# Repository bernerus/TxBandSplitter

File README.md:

# TxBandSplitter
SDR Transmit band splitter and amplifier for VHF/UHF bands. A KiCad + Python project.

The aim of this project is to create an intermediate transmit driver stage that 
takes the RF level of an SDR transmitter from around 1 dBm to around +30 dBm.
Doing this would probably be illegal except for licensed radio amateurs, but
such equipment should nevertheless work only on the amateur bands.
This device takes 1 dBm RF from e.g. a HackRF transceiver, splits the output on
either the 50, 144, 432 och 1295 MHz bands and takes the output level to about +30 dBm or 1 W.
The amplification is done in two steps with the filtering and a programmable attenuator in between,
The final RF is the again split on 4 outputs usein PIN diodes.

The band selection, amplifier power and level of attenuation is controlled over an I2C connection
suitable for connectiong to a RaspBerry PI computer.

Sample software for controlling the device from an RPI is written in Python.

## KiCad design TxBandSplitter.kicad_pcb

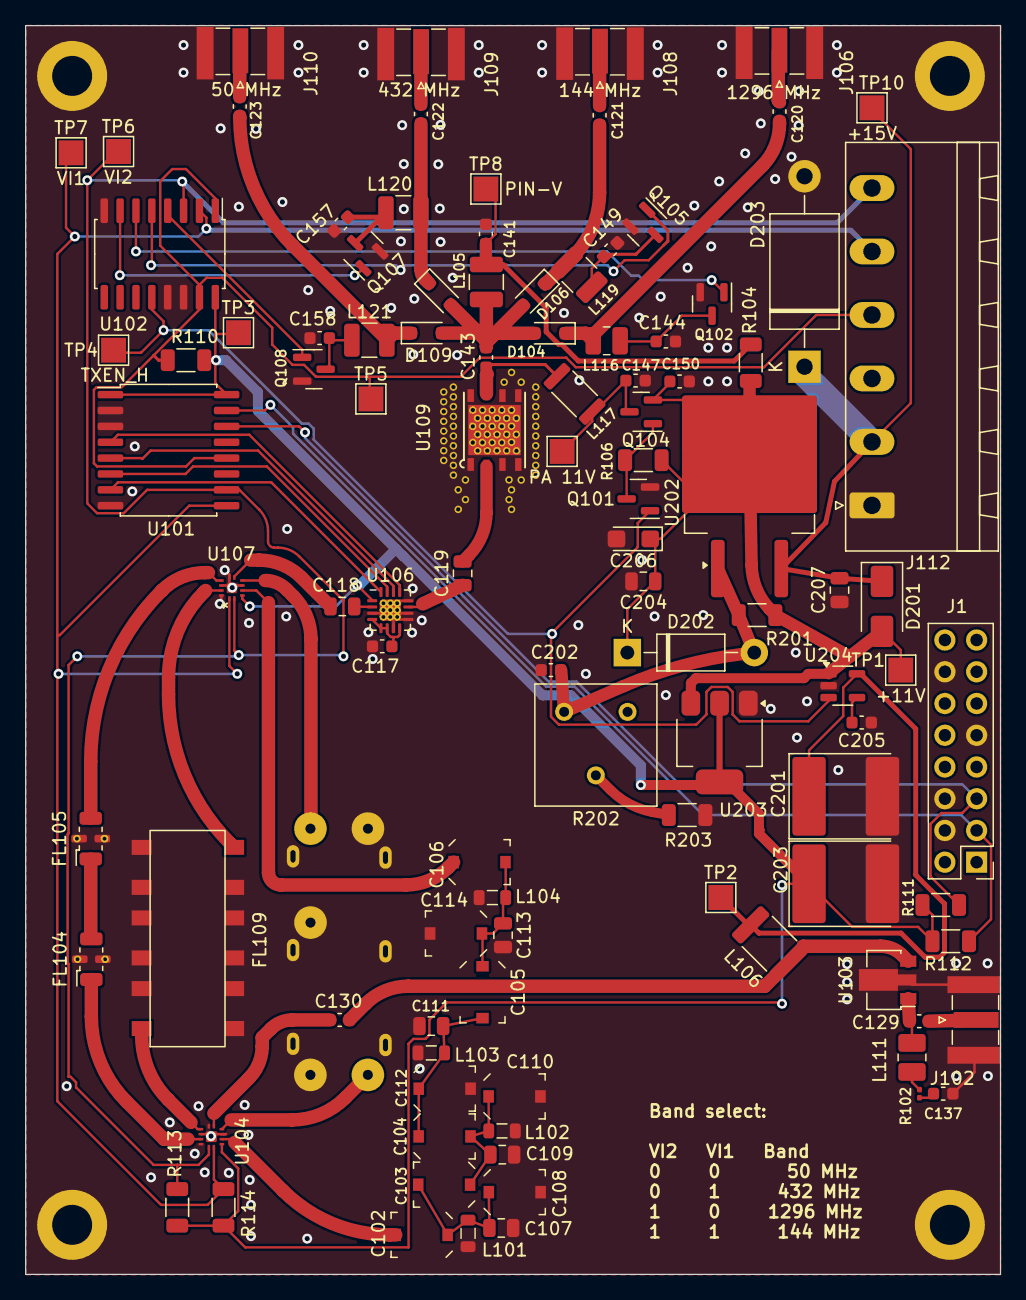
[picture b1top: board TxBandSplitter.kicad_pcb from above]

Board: 2 copper layers, 78.0 x 99.9 mm, 109 parts (1 on the bottom side), 63 nets.

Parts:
C102, C106, C108, C110, C112, C114: 5-20pF; C_Trimmer_Murata_TZC3
C103, C104, C105: 2.5-6pF; C_Trimmer_Murata_TZC3
C107, C113: 100pF; C_0805_2012Metric
C109, C111: 120pF; C_0805_2012Metric
C117, C120, C121: 1nF; C_0603_1608Metric
C118, C119: 1nF; C_0805_2012Metric
C122, C123, C129, C130, C141, C143, C144, C147, C149, C150, C157, C158, C205: 10nF; C_0603_1608Metric
C137: 330pF; C_0603_1608Metric
C201: 2.2μF; CP_EIA-7260-38_AVX-R_Pad2.68x6.30mm_HandSolder
C202: 10μF; C_0603_1608Metric
C203: 10μF; CP_EIA-7260-38_AVX-R_Pad2.68x6.30mm_HandSolder
C204, C207: 0.1μF; C_0805_2012Metric
C206: 1μF 16V Tantal; CP_EIA-3216-18_Kemet-A
D104, D106, D107, D109: BA592; D_SOD-323_HandSoldering
D201: LL4002; D_SMA
D202: LL4002; D_DO-41_SOD81_P10.16mm_Horizontal
D203: 1.5KE18A; D_DO-201AE_P15.24mm_Horizontal
FL101: FE-7H3-160A; FE-7H3-160
FL104: HFCN-1200+; Filter_Mini-Circuits_FV1206
FL105: LFCN-1325; Filter_Mini-Circuits_FV1206
FL109: FE-1069; 5CHT
H101, H102, H103, H104: MountingHole_Pad; MountingHole_3.2mm_M3_DIN965_Pad
J1: Raspberry_Pi 16-pin; PinHeader_2x08_P2.54mm_Vertical
J102, J106, J108, J109, J110: SMA; SMA_Samtec_SMA-J-P-X-ST-EM1_EdgeMount
J112: Conn_01x06_Pin; PhoenixContact_MSTBA_2,5_6-G-5,08_1x06_P5.08mm_Horizontal
L101, L102, L103, L104: 68 nH; L_0805_2012Metric
L105: 5.6uH; L_1210_3225Metric
L106, L117: WA8514-AE; L_1812_4532Metric
L111: 680nH; L_1008_2520Metric_Pad1.43x2.20mm_HandSolder
L116: 680 nH; L_1008_2520Metric
L119: 1.8uH; L_1210_3225Metric
L120: 5,6 uH; L_1210_3225Metric
L121: 15 uH; L_1210_3225Metric
Q101, Q102, Q105, Q107, Q108: BSS138; SOT-23
Q104: FDN358P; SOT-23
R102: 150; R_0201_0603Metric
R104: 270; R_1206_3216Metric
R106, R110, R111, R112, R113, R114: 10k; R_1206_3216Metric
R201, R203: 220; R_1206_3216Metric
R202: 1k; Potentiometer_Bourns_3386F_Vertical
TP1: +11V; TestPoint_Pad_2.0x2.0mm
TP2: VCC; TestPoint_Pad_2.0x2.0mm
TP3: VDD; TestPoint_Pad_2.0x2.0mm
TP4: TXEN_H; TestPoint_Pad_2.0x2.0mm
TP5: TXEN_L; TestPoint_Pad_2.0x2.0mm
TP6: VI2; TestPoint_Pad_2.0x2.0mm
TP7: VI1; TestPoint_Pad_2.0x2.0mm
TP8: PIN-V; TestPoint_Pad_2.0x2.0mm
TP9: PA 11V; TestPoint_Pad_2.0x2.0mm
TP10: +15V; TestPoint_Pad_2.0x2.0mm
U101: PCF8574; SOIC-16W_7.5x10.3mm_P1.27mm
U102: 4555; SO-16_5.3x10.2mm_P1.27mm
U103: PGA-103+; SOT-89-3
U104, U107: RFSW6042; QFN12_RFSW_QOR
U106: SKY12348-350LF; QFN-16-1EP_3x3mm_P0.5mm_EP1.7x1.7mm_ThermalVias
U109: PHA-202+; PHA202+
U202: LM317D2T; TO-263-2
U203: LD1117S33TR_SOT223; SOT-223-3_TabPin2
U204: LP2985-5.0; SOT-23-5

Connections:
+11V: C150.1, C204.1, C206.1, D201.2 (A), D202.1 (K), Q104.2 (S), R104.2, R106.1, R201.1, TP1.1, U202.2 (VO), U203.3 (VI), U204.1 (VIN)
/Power/+15V: C207.2, D201.1 (K), D203.1 (K), J112.2, TP10.1, U202.3 (VI)
/RF1: C130.1, L106.2, U103.3
/RFCIN: C130.2, U104.7 (ANT)
/RFOUT2: C121.2, D106.1 (K), L119.2
/RFOUT6: C123.2, D109.1 (K), L121.2
/RFOUT23: C120.2, D104.1 (K), L116.2
/RFOUT70: C122.2, D107.1 (K), L120.2
/RF_In: C129.1, J102.1 (In)
/RF_Out_2m: C121.1, J108.1 (In)
/RF_Out_6m: C123.1, J110.1 (In)
/RF_Out_23cm: C120.1, J106.1 (In)
/RF_Out_70cm: C122.1, J109.1 (In)
/SCL: J1.5 (SCL/GPIO3), R111.2, U101.14 (SCL)
/SDA: J1.3 (SDA/GPIO2), R112.2, U101.15 (SDA)
/TXEN_H: Q101.1 (G), TP4.1, U102.12 (Q0), U204.3 (ON/~OFF)
/TXEN_L: J112.4, R110.2, TP5.1, U101.12 (P7), U102.1 (~EN), U102.15 (~EN)
GND: C107.2, C108.2, C109.2, C110.2, C111.2, C112.2, C113.2, C114.2, C117.1, C137.2, C141.1, C144.1, C147.1, C149.1, C150.2, C157.1, C158.1, C201.2, C202.1, C203.2, C204.2, C205.1, C206.2, C207.1, D203.2 (A), FL101.1 (IN-), FL101.3 (OUT-), FL101.GND (MID-), FL104.2 (GND), FL104.4 (GND), FL105.2 (GND), FL105.4 (GND), FL109.2 (GND), FL109.8 (GND), FL109.GND, H101.1, H102.1, H103.1, H104.1, J1.4 (GND), J1.6 (GND), J1.9 (GND), J1.14 (GND), J102.2 (Ext), J106.2 (Ext), J108.2 (Ext), J109.2 (Ext), J110.2 (Ext), J112.1, L101.2, L102.2, L103.2, L104.2, Q101.2 (S), Q102.2 (S), Q105.2 (S), Q107.2 (S), Q108.2 (S), R203.2, U101.2 (A1), U101.3 (A2), U101.8 (VSS), U102.8 (Vss), U102.13 (A1), U102.14 (A0), U103.2 (GND), U104.5 (GND), U104.8 (GND), U104.10 (GND), U104.12 (GND), U104.13 (EPAD), U106.3 (NC), U106.7 (NC), U106.9 (NC), U106.10 (NC), U106.12 (NC), U106.17 (GND), U107.5 (GND), U107.8 (GND), U107.10 (GND), U107.12 (GND), U107.13 (EPAD), U109.EP, U109.GND, U203.1 (GND), U204.2 (GND)
unnamed: C102.1, C103.2, C107.1, C108.1, L101.1
unnamed: C103.1, C104.2, C109.1, C110.1, L102.1
unnamed: C104.1, C105.2, C111.1, C112.1, L103.1
unnamed: C105.1, C106.2, C113.1, C114.1, L104.1
unnamed: C129.2, L111.1, U103.1
unnamed: C137.1, R102.2
unnamed: C141.2, L105.2, R104.1, TP8.1
unnamed: C143.2, D104.2 (A), D106.2 (A), D107.2 (A), D109.2 (A), L105.1
unnamed: C202.2, D202.2 (A), R201.2, R202.1, U202.1 (ADJ)
unnamed: FL101.5 (IN+), U107.6 (RF3)
unnamed: FL101.2 (OUT+), U104.6 (RF3)
unnamed: FL104.1 (IN), U104.11 (RF2)
unnamed: FL104.3 (OUT), FL105.1 (IN)
unnamed: FL105.3 (OUT), U107.9 (RF1)
unnamed: FL109.1 (IN), U104.9 (RF1)
unnamed: FL109.7 (OUT), U107.11 (RF2)
unnamed: L111.2, R102.1
unnamed: Q101.3 (D), Q104.1 (G), R106.2
unnamed: C144.2, L116.1, Q102.3 (D)
unnamed: Q102.1 (G), U102.6 (Q2)
unnamed: C147.2, L117.1, Q104.3 (D), TP9.1
unnamed: C149.2, L119.1, Q105.3 (D)
unnamed: Q105.1 (G), U102.5 (Q1)
unnamed: C157.2, L120.1, Q107.3 (D)
unnamed: Q107.1 (G), U102.7 (Q3)
unnamed: C158.2, L121.1, Q108.3 (D)
unnamed: Q108.1 (G), U102.4 (Q0)
unnamed: R202.2, R203.1
unnamed: U101.4 (P0), U106.13 (V1)
unnamed: U101.5 (P1), U106.14 (V2)
unnamed: U101.6 (P2), U106.15 (V3)
unnamed: U101.7 (P3), U106.16 (V4)
unnamed: C102.2, U104.4 (RF4)
unnamed: C118.2, U106.2 (RF1)
unnamed: C119.1, U106.11 (RF2)
unnamed: C117.2, U106.4 (RFGND1), U106.5 (RFGND2), U106.6 (RFGND3), U106.8 (RFGND4)
unnamed: C118.1, U107.7 (ANT)
unnamed: C106.1, U107.4 (RF4)
unnamed: C143.1, L117.2, U109.OUT (RF_OUT)
unnamed: C205.2, U204.4 (BP)
RF_Filtered: C119.2, U109.IN (RF_IN)
VCC: C201.1, L106.1, TP2.1, U204.5 (VOUT)
VDD: C203.1, R110.1, R111.1, R112.1, R113.1, R114.1, TP3.1, U101.1 (A0), U101.16 (VDD), U102.16 (Vdd), U104.3 (VDD), U106.1 (VDD), U107.3 (VDD), U203.2 (VO)
VI1: J112.5, R114.2, TP7.1, U101.9 (P4), U102.2 (A0), U104.2 (C1), U107.1 (C2)
VI2: J112.6, R113.2, TP6.1, U101.10 (P5), U102.3 (A1), U104.1 (C2), U107.2 (C1)

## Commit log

2024-06-13 Initial commit representing version 4 of this project
2024-06-15 Added python code and appropriate .gitignores
2024-06-15 Changed name of power schematic
